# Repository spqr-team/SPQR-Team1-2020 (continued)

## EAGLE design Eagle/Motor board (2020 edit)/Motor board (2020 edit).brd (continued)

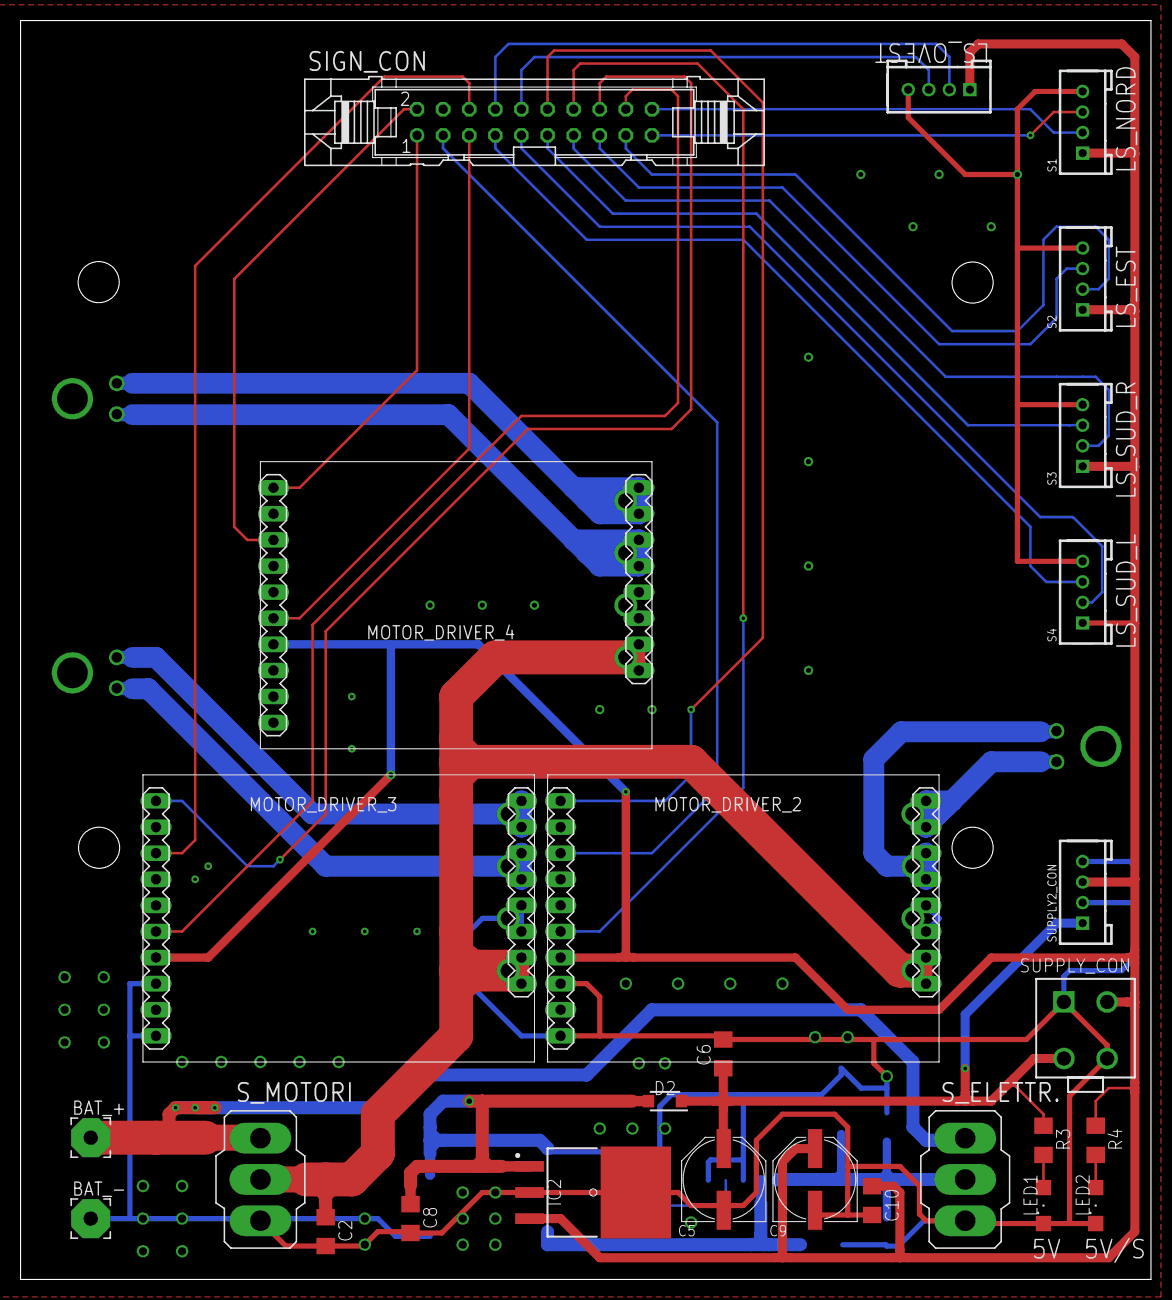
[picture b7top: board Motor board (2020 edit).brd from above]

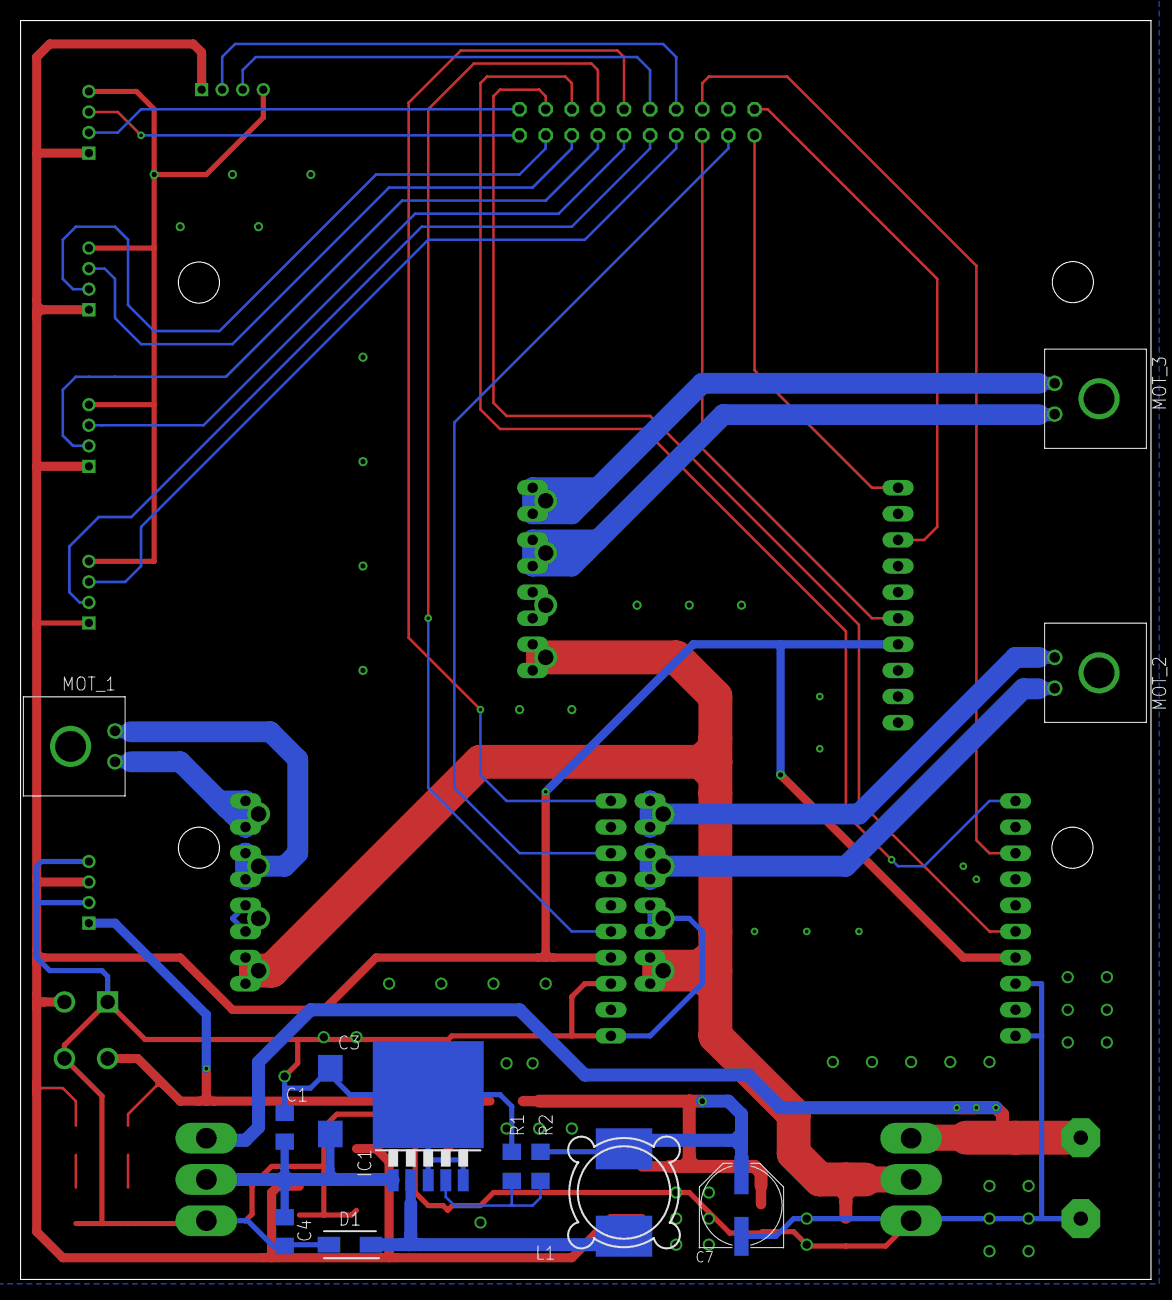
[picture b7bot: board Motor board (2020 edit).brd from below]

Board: 2 copper layers, 110.0 x 122.5 mm, 39 parts (12 on the bottom side), 36 nets.

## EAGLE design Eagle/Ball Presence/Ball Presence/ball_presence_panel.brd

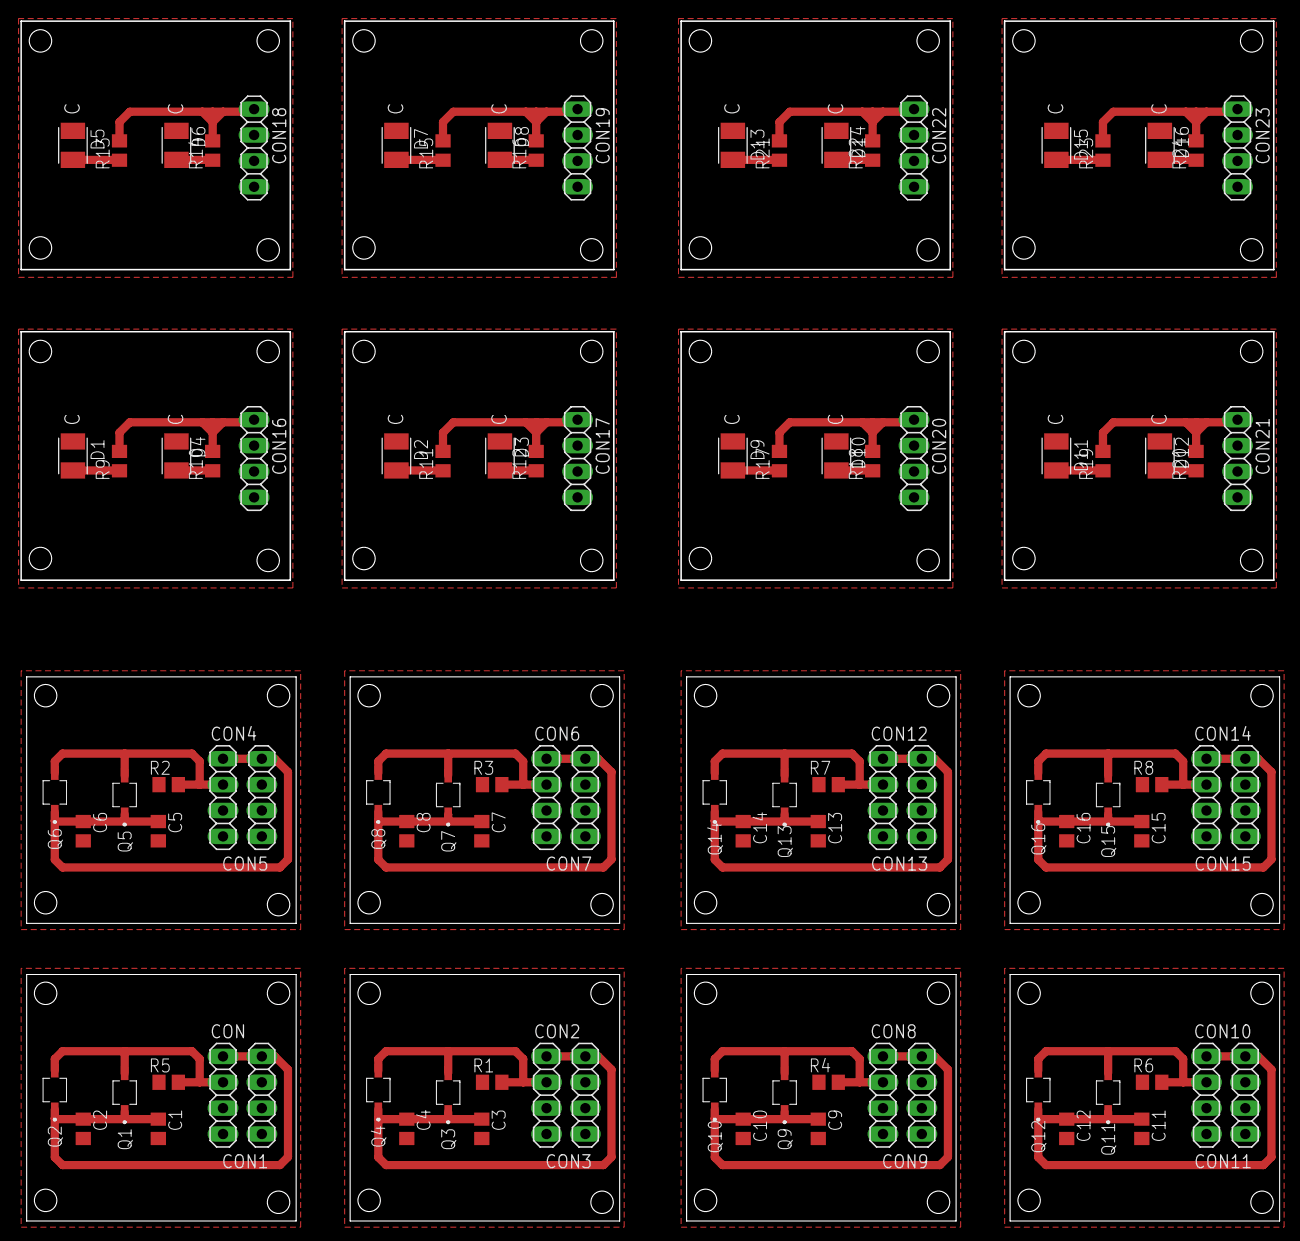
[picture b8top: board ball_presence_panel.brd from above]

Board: 2 copper layers, 123.5 x 117.8 mm, 96 parts (0 on the bottom side), 56 nets.

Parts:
C1, C2, C3, C4, C5, C6, C7, C8, C9, C10, C11, C12, C13, C14, C15, C16: C0805
CON, CON1, CON2, CON3, CON4, CON5, CON6, CON7, CON8, CON9, CON10, CON11, CON12, CON13, CON14, CON15, CON16, CON17, CON18, CON19, CON20, CON21, CON22, CON23: 1X04
D1, D2, D3, D4, D5, D6, D7, D8, D9, D10, D11, D12, D13, D14, D15, D16: 3528-2PIN
Q1, Q2, Q3, Q4, Q5, Q6, Q7, Q8, Q9, Q10, Q11, Q12, Q13, Q14, Q15, Q16: VEMT2520X01
R1, R2, R3, R4, R5, R6, R7, R8, R9, R10, R11, R12, R13, R14, R15, R16, R17, R18, R19, R20, R21, R22, R23, R24: R0805

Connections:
GND: C1.2, C2.2, CON.4, CON1.4, R5.1
GND1: C3.2, C4.2, CON2.4, CON3.4, R1.1
GND2: C5.2, C6.2, CON4.4, CON5.4, R2.1
GND3: C7.2, C8.2, CON6.4, CON7.4, R3.1
GND4: C9.2, C10.2, CON8.4, CON9.4, R4.1
GND5: C11.2, C12.2, CON10.4, CON11.4, R6.1
GND6: C13.2, C14.2, CON12.4, CON13.4, R7.1
GND7: C15.2, C16.2, CON14.4, CON15.4, R8.1
GND8: CON16.4, D1.1, D4.1
GND9: CON17.4, D2.1, D3.1
GND10: CON18.4, D5.1, D6.1
GND11: CON19.4, D7.1, D8.1
GND12: CON20.4, D9.1, D10.1
GND13: CON21.4, D11.1, D12.1
GND14: CON22.4, D13.1, D14.1
GND15: CON23.4, D15.1, D16.1
unnamed: D1.2, R9.1
unnamed: D2.2, R11.1
unnamed: D3.2, R12.1
unnamed: D4.2, R10.1
unnamed: D5.2, R13.1
unnamed: D6.2, R14.1
unnamed: D7.2, R15.1
unnamed: D8.2, R16.1
unnamed: D9.2, R17.1
unnamed: D10.2, R18.1
unnamed: D11.2, R19.1
unnamed: D12.2, R20.1
unnamed: D13.2, R21.1
unnamed: D14.2, R22.1
unnamed: D15.2, R23.1
unnamed: D16.2, R24.1
SIG1: CON.2, Q1.2, Q2.2, R5.2
SIG2: CON2.2, Q3.2, Q4.2, R1.2
SIG3: CON4.2, Q5.2, Q6.2, R2.2
SIG4: CON6.2, Q7.2, Q8.2, R3.2
SIG5: CON8.2, Q9.2, Q10.2, R4.2
SIG6: CON10.2, Q11.2, Q12.2, R6.2
SIG7: CON12.2, Q13.2, Q14.2, R7.2
SIG8: CON14.2, Q15.2, Q16.2, R8.2
V+: C1.1, C2.1, CON.1, CON1.1, Q1.1, Q2.1
V+1: C3.1, C4.1, CON2.1, CON3.1, Q3.1, Q4.1
V+2: C5.1, C6.1, CON4.1, CON5.1, Q5.1, Q6.1
V+3: C7.1, C8.1, CON6.1, CON7.1, Q7.1, Q8.1
V+4: C9.1, C10.1, CON8.1, CON9.1, Q9.1, Q10.1
V+5: C11.1, C12.1, CON10.1, CON11.1, Q11.1, Q12.1
V+6: C13.1, C14.1, CON12.1, CON13.1, Q13.1, Q14.1
V+7: C15.1, C16.1, CON14.1, CON15.1, Q15.1, Q16.1
V+8: CON16.1, R9.2, R10.2
V+9: CON17.1, R11.2, R12.2
V+10: CON18.1, R13.2, R14.2
V+11: CON19.1, R15.2, R16.2
V+12: CON20.1, R17.2, R18.2
V+13: CON21.1, R19.2, R20.2
V+14: CON22.1, R21.2, R22.2
V+15: CON23.1, R23.2, R24.2

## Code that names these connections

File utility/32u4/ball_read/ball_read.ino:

/**
  Sensor Mapping
    Sensor  Angle Pin Port
    S1      0     26  PD6
    S2            25  PD4
    S3            19  PD1
    S4            18  PD0
    S5      90    1   PE6
    S6            40  PF1
    S7            39  PF4
    S8            38  PF5
    S9      180   37  PF6
    S10           36  PF7
    S11           32  PC7
    S12           31  PC6
    S13     270   30  PB6
    S14           29  PB5
    S15           28  PB4
    S16           27  PD7
    loop cycle duration: 3.2 millis
**/

#define S5 ((PINE & 64 ) >> 6)

#define S11 ((PINC & 128 ) >> 7)
#define S12 ((PINC & 64 ) >> 6)

#define S13 ((PINB & 64 ) >> 6)
#define S14 ((PINB & 32 ) >> 5)
#define S15 ((PINB & 16) >> 4)

#define S1 ((PIND & 64 ) >> 6)
#define S2 ((PIND & 16 ) >> 4)
#define S3 ((PIND & 2 ) >> 1)
#define S4 (PIND & 1 )
#define S16 ((PIND & 128) >> 7)

#define S6 ((PINF & 2 ) >> 1)
#define S7 ((PINF & 16 ) >> 4)
#define S8 ((PINF & 32 ) >> 5)
#define S9 ((PINF & 64 ) >> 6)
#define S10 ((PINF & 128 ) >> 7)

#define NCYCLES 255
#define BROKEN  230
#define TOO_LOW 45

#define LED1ON (PORTD = PORTD | 0b00100000)
#define LED1OFF (PORTD = PORTD & 0b11011111)

#define LED2ON (PORTF = PORTF | 0b00000001)
#define LED2OFF (PORTF = PORTF & 0b11111110)

#define LED3ON (PORTB = PORTB | 0b10000000)
#define LED3OFF (PORTB = PORTB & 0b01111111)

#define LED4ON (PORTB = PORTB | 0b00000001)
#define LED4OFF (PORTB = PORTB & 0b11111110)


int counter[16];
int distance;
int nmax = 0;
int sensor = 0;

int oldIndex = 0;
int oldDistance = 0;

byte ballInfo = 0;

float xs[16];
float ys[16];

float angle = 0;
int dist = 0;
boolean sending = false;
byte sendAngle = 0, sendDistance = 0;
byte sendByte = 0;

unsigned long t = 0;

void setup() {
  delay(1000);

  Serial.begin(57600);
  Serial1.begin(57600);

  
  /*For now replace pinMode with writes to the direction register. 
    We don't know if pinMode will work on those sensors, and it has proven not be working on digitalWrite for reasons probably relative to compatibility between Arduino and our board,
    but this needs further investigation*/  

  //Set the LEDs as outputs, keep the rest as input by default

  //LED3(PB7) and LED4 (PB0)
  DDRB |= 0b10000001;
  //LED2 (PF0)
  DDRF |= 0b00000001;
  //LED1 (PD5)
  DDRD |= 0b00100000;
  
  /*pinMode(26, INPUT);   //S1
  pinMode(25, INPUT);   //S2
  pinMode(19, INPUT);   //S3
  pinMode(18, INPUT);   //S4
  pinMode(1, INPUT);    //S5
  pinMode(40, INPUT);   //S6
  pinMode(39, INPUT);   //S7
  pinMode(38, INPUT);   //S8
  pinMode(37, INPUT);   //S9
  pinMode(36, INPUT);   //S10
  pinMode(32, INPUT);   //S11
  pinMode(31, INPUT);   //S12
  pinMode(30, INPUT);   //S13
  pinMode(29, INPUT);   //S14
  pinMode(28, INPUT);   //S15
  pinMode(27, INPUT);   //S16*/
  
  for (int i = 0; i < 16; i++) {
    xs[i] = cos((22.5 * PI / 180) * i);
    ys[i] = sin((22.5 * PI / 180) * i);
  }
}

void loop() {
  readBallInterpolation();
  //printCounter();
  sendDataInterpolation();
  readFromTeensy();
  //test();
  //delay(100);
}

/**--- READ BALL USING SENSORS ANGLE INTERPOLATION ---**/

void readBallInterpolation() {
  for (int i = 0; i < 16; i++) {
    counter[i] = 0;
  }

  //reads from the register
  for (int i = 0; i < NCYCLES; i++) {
    counter[0] += !S1;
    counter[1] += !S2;
    counter[2] += !S3;
    counter[3] += !S4;
    counter[4] += !S5;
    counter[5] += !S6;
    counter[6] += !S7;
    counter[7] += !S8;
    counter[8] += !S9;
    counter[9] += !S10;
    counter[10] += !S11;
    counter[11] += !S12;
    counter[12] += !S13;
    counter[13] += !S14;
    counter[14] += !S15;
    counter[15] += !S16;
  }

  float x = 0, y = 0;
  for (int i = 0; i < 16; i++) {
    if (counter[i] > BROKEN || counter[i] < TOO_LOW) counter[i] = 0;

    x += xs[i] * counter[i];
    y += ys[i] * counter[i];
  }

  angle = atan2(y, x) * 180 / PI;
  angle = ((int)(angle + 360)) % 360;

  //distance is 0 when not seeing ball
  //dist = hypot(x, y);
  
  nmax = 0;
  //saves max value and sensor
  for (int i = 0; i < 16; i++) {
    if (counter[i] > nmax) {
      nmax = counter[i];
      sensor = i;
    }
  }

  distance = nmax;
  
  //turn led on
  if (distance == 0) {
    LED1OFF;
  } else {
    LED1ON;
  }
}

unsigned long sendtimer = 0;

void sendDataInterpolation() {
  //We must ensure that each number is expressed with three digits, adding leading zeros if necessary, to further improve transmission reliability
  String str_angle = String((int) angle, DEC);
  String str_distance = String(NCYCLES - (int) distance, DEC);

  String sendStr_angle = "";
  String sendStr_distance = "";

  if(str_angle.length() == 1) sendStr_angle = "00" + str_angle;
  else if(str_angle.length() == 2) sendStr_angle = "0" + str_angle;
  else sendStr_angle = str_angle;
  
  if(str_distance.length() == 1) sendStr_distance = "00" + str_distance;
  else if(str_distance.length() == 2) sendStr_distance = "0" + str_distance;
  else sendStr_distance = str_distance;

  //slow down the communciation a little bit, or it might get very messy
  if(millis() - sendtimer > 40){
    Serial1.print("b");
    Serial1.print(sendStr_angle);
    Serial1.print("-");
    Serial1.print(sendStr_distance);
    Serial1.print("IB");
    sendtimer = millis();
  }

}

void test() {
  readBallInterpolation();
  
  Serial1.println("===========");
  Serial1.print(S1);
  Serial1.print(" | ");
  Serial1.print(S2);
  Serial1.print(" | ");
  Serial1.print(S3);
  Serial1.print(" | ");
  Serial1.print(S4);
  Serial1.print(" | ");
  Serial1.print(S5);
  Serial1.print(" | ");
  Serial1.print(S6);
  Serial1.print(" | ");
  Serial1.print(S7);
  Serial1.print(" | ");
  Serial1.print(S8);
  Serial1.print(" | ");
  Serial1.print(S9);
  Serial1.print(" | ");
  Serial1.print(S10);
  Serial1.print(" | ");
  Serial1.print(S11);
  Serial1.print(" | ");
  Serial1.print(S12);
  Serial1.print(" | ");
  Serial1.print(S13);
  Serial1.print(" | ");
  Serial1.print(S14);
  Serial1.print(" | ");
  Serial1.print(S15);
  Serial1.print(" | ");
  Serial1.print(S16);
  Serial1.print(" ---  ");
  Serial1.println(sensor);
  Serial1.println("===========");
  delay(100);

}


void printCounter() {
  for (int i = 0; i < 16; i++) {
    Serial1.print(counter[i]);
    Serial1.print(" | ");
  }
    Serial1.print("\t\t| Angle: " );
    Serial1.print(angle);
    Serial1.print("||| Distance: " );
    Serial1.print(distance);
    
  Serial1.println();
  delay(100);
}

void readFromTeensy(){
  while(Serial1.available()){
    byte b = Serial1.read();
    if(b & 0b00000001 == 1) LED2ON;
    else LED2OFF;
    if((b & 0b00000010) >> 1 == 1) LED3ON;
    else LED3OFF;
    if((b & 0b00000100) >> 2 == 1) LED4ON;
    else LED4OFF;
  }
}

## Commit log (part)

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2019-10-09 culo
2019-10-14 culetto
2019-10-21 First class structure
2019-10-21 Maybe now it less confusing
2019-10-21 New code working with imu reading, tests are not working currently
2019-10-27 Branch classi latino, IMU MOT PID
2019-10-28 meno mot
2019-11-11 Added motor support, should work out of the box
2019-11-12 corretta una boiata
2019-11-13 Motors and recenter working
2019-11-14 init hardware
2019-11-18 adding a bit of polymorphism
2019-11-18 ball, maybe
2019-11-18 Using enums instead of ints for transmission protocols
2019-11-18 implemented camera
2019-11-18 added camera
2019-11-25 started working on the us sensors
2019-11-25 finished us, having trouble testing
2019-11-27 Error compiling, syntax should be better
2019-11-27 Finally us working
2019-12-02 US sensors using DataSourceController now working
2019-12-02 having troubles testing
2019-12-03 ema scemo
2019-12-04 first trial to follow the ball
2019-12-05 started writing goalie(), kinda dumb but seems to work
2019-12-05 Lines not working well, fixed missing initializations that caused the code to crash
2019-12-05 lines now working: angle of each motor was est to 0 in constructor
2019-12-05 sbubabub
2019-12-05 fixed something left by u-siri-ous
2019-12-09 ported goalie and keeper from old code, condtion code working to decide game strategy
2019-12-09 forgot to save a file
2019-12-11 started porting bt, corrected smth
2019-12-17 position
2019-12-20 started line_system to play properly
2019-12-26 reimproted the zone position system
2020-01-15 fixed a major issues with linesystems
2020-01-15 aaaa
2020-01-15 First camera script for conic shaped mirror
2020-01-20 conic shaped camera mirror final script
2020-01-20 new protocol for camera
2020-01-20 aaaaaaa
2020-01-22 first hardware commit
2020-01-22 working camera->teensy transimission protocol
2020-01-22 new goalie c:
2020-01-22 Teensy pinout done, supply almost done, IMU done
2020-01-22 Added motor drivers to schematic
2020-01-24 Added 32U4, created OpenMV4 library
2020-01-25 Added camera and IMU, ATmega32U4 pinout done, added motor drivers' leds
2020-01-26 Added motor connectors, added electrolytic cap on supply
2020-01-26 Calculating angles with the camera, have to be fixed with the 90 degrees offset. Uploading a little teesny <-> atmega32u4 test script for bidirectional relaiable serial communication
2020-01-27 Angles working?
2020-01-27 Angles finally working
2020-01-27 Added every component in BoM
2020-01-27 BoM finished
2020-01-28 Supply planes for motor drivers done
2020-01-29 reintroduces semi axis locking. Some bug with the lines make the robot stop when it gets on one. Tilt with vshaped mirror reintroduced
2020-01-31 Fixed camera angle reading from both openmv and teensy. Tilt from goalie kinda working now
2020-02-03 Camera angle correction using IMU should now work correctly
2020-02-03 Camera angle fix using IMU working once for all
2020-02-03 storcimento kinda working
2020-02-04 PCB layout almost done
2020-02-04 PCB almost done
2020-02-05 slight modifies to camera
2020-02-08 Fixed silkscreen errors
2020-02-10 Cleaned useless files, added datasheets
2020-02-10 Now using arduino PID library for movements. There probably a better way to use this, but it works for now
2020-02-10 corrected a few errors, Furio plays is more precise than ever when playing
2020-02-12 not working
2020-02-12 Added safety resistances on Teensy > VNH traces
2020-02-17 now latest complete structs are copied into new ones when updating status vector
2020-02-17 camera recenter (on x axis) working c:
2020-02-17 experimenting with y axis
2020-02-17 ema taking over
2020-02-17 slight edits to goalie
2020-02-17 Now using Flavio's PID Library, plays flawlessly
2020-02-18 Now using status vector everywhere :D (To be tested)
2020-02-21 New conic shaped mirror, works better. It's higher and has more noticeable changes on the y axis
2020-02-26 aaaaaaaaaaaaaaaaA
2020-02-26 camera pid testing
2020-02-26 complementary filter object
2020-02-27 now the robot can use the camera to recenter even when one the goals can't be seen
2020-02-28 Added RCWL compatible ToF
2020-02-28 camera working
2020-02-29 organized code in 5 folders, left vars.h and main.cpp out of them for easy changing purposes. also did two currently_unused folder in sensors for us and things soon-to-be taken out from the robot (li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
2020-02-29 updated README.md
    we now have names and such
2020-02-29 still README.md
    ocd much?
2020-03-02 little correction to the pid for position
2020-03-02 camera lines
2020-03-02 Corrected a few major bugs in camera data receiving and using. Still no lock trying to directly fix goals' coordinates using axis rotation formula.
2020-03-02 Job finished. Ready to print
2020-03-02 Create LICENSE
2020-03-03 added testMenu, to be tested
2020-03-03 still test menu, still to test
2020-03-09 edits in camera
2020-03-12 looking at past days' work
2020-03-12 fix last merge
2020-03-14 started thinking about goalie, to be tested, dunno if it works
2020-05-05 first commit, starting to work with a new setup
2020-05-05 removed data_source_us.h/.cpp, no US present on the 2021 robot, if needed, the files can be found in branch master
2020-05-06 fixed motor angles
2020-06-02 FILE DECRISTO
2020-10-29 implement test menu in main loop
2020-10-29 recycle striker strategy from last year code
    bad translation, goalie is actually a striker
2020-10-31 disable vector sum code for now
    calculations are a bitty crappy, think I found the bug for now (check added comments)
2020-10-31 a bit of recalibration for everything for the presentation game
2020-11-04 reorder files into system folders
    also rename Goalie to Striker because GRAMMAR
    (Goalie actually means keeper but we always intended it as a striker :D)
2020-11-21 port ball reading code to 32u4
2020-11-29 update ball_read to use registers instead of pinMode and digitalWrite also move all the files relative to 32u4 uC inside a dedicated folder add the Blink script i made to test if everything was worki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
2020-12-14 fix a "little" problematic derp in Main Board The labels for PowerBlock 4 's RC filter resistor and capacitor were inverted And so we soldered the components inverted, and we had a short between VCC 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
2020-12-17 test: add a couple of tests for 32u4
2021-01-11 pid: recalibrate pid
2021-01-11 use 5kHz as pwm frequency for motors So we don't get the motors stopping to turn when changing direction at high speeds because of current limit on the vnh7070
2021-01-11 systems: introduce empty systems for testing purposes
2021-01-11 do not update usCtrl They're not on the robot, they're not defined in the code, and updating them will just cause the whole thing to crash
2021-01-11 ball_read: tweak values for a good reading
2021-01-11 strategy: introduce a test striker with empty systems and set as only role
2021-01-11 movement: correct pid formula and motors angles
2021-01-15 bluetooth: sm2 test script
2021-01-31 game: fix order of updating that causes crashes
2021-01-31 camera: update scripts, line and position handling for H7
2021-01-31 roles: go back to normal striker
2021-01-31 pins: update buzzer and switches pins
2021-02-01 fix short between S11 and Multi1 GND
2021-02-01 do not initialize LEDs
    LEDs are hookep up to the AtMega32U4on the new board
    Some LED pins are hooked up to line sensors on the new board and caused them not to work properly
2021-02-22 new docs branch for docs, with a copy of the code just in case
2021-02-22 motors: ramp up and slow down of motors instead of bang.bang
2021-02-23 camera: tweaks to OpenMV script
    also add a control on the position of the blue goal
2021-03-01 remove old unused line systems
2021-03-01 striker: use striker based on old Latino's code
2021-03-01 sys-camera: a bit of recalibration
2021-03-01 motors: complementary filter on a per-motor speed
    avoid all the cons of bang-bang without spending 5mS ramping up and down
2021-03-01 add a missing pragma once
2021-03-01 positionsys camera: introduce an easy way to counter act bad mirror positioning This allows to define each point relative to the absolute center of the field shifting each Move Setpoint by a defined 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
2021-03-22 movement: enable vector sum for multiple movements in a single cycle
2021-03-29 ball sensor: ball angle in absolute space
2021-04-13 Final commit
2021-04-13 Switched powerblock 4 filter labels
2021-04-14 test menu: complete refactor
    and add camera tilt test
2021-04-14 complementary filter: default init of variable which may have caused crashes
2021-04-14 keeper: small value tweaking
2021-04-14 striker: robot tilt towards the goal when attacking Although without a roller the robot just sky-rockets the ball away when they come in touch
2021-04-14 position system camera & motors: proper vector sum, value tweaking
2021-04-14 OpenMV H7: avoid crash when blue goal isn't in sight
2021-04-19 Camera sensor: correct a massive freaking typo This caused a huge bug when testing the striker i'm dumb
2021-04-19 tilt: better tilt
2021-04-19 camera: coords filtering and better route calculation
2021-05-07 we now have a roller
2021-05-10 preparation for romecup: refine striker
2021-05-10 robocup preparation: fix lines add a workaround for when we don't see either of the goals add nice startup sounds
2021-05-10 drive: only drive when the PID is calculated no need to recalibrate the pid
2021-05-11 camera: translate camera points in raw data, not in position system
2021-05-12 robocup preparation: correct pos-sys-camera bugs better use of roller nice startup/debugging sounds disable auto gain in H7
2021-05-13 romecup: precision shooter
2021-05-13 mix fixes git decided to cancel
2021-05-13 precision shooter
2021-05-13 disable keeper for now
    as it looks like sometimes it blocks code execution
2021-05-13 --amend
2021-05-13 bluetooth, at last
2021-05-14 even better pass and shoot
2021-05-14 latest romecup code
2021-05-28 striker: follow the ball, pick it and score
    Our roller is about to fall apart and i have no specific sensor to detect the ball, which means in perfect conditions it works but it really doesn't in real world conditions
    Also we need to ameliorate the communication protocol between teensy and 32u4 in order to not lose precision
2021-05-29 ball: new ball reading algorithm, should improve precision
2021-06-07 initial ball presence sensors
    line sensors but small
2021-06-09 started dividing folders
2021-06-10 ball presence sensor v1.0
2021-06-20 ball presence sensor basically a line sensor with split led and phototransistors
2021-06-20 drive: fix to accept tilt values in the [0,360] range
2021-06-20 precision shooter: catch and spinning kick
2021-06-21 precision shooter,camera: improve, fix math error in translation alongside with better speed calculation and utility methods
2021-06-21 not used, using drive with new folders
2021-06-21 precision shooter: improve spinning kick
2021-06-22 precision shooter: catches ball and goes towards goal
    depending on the angle it catches the ball at, sometimes it hides the ball, sometimes it does a random spinning kick when it founds the line
2021-06-22 striker-roller: complete striker using the roller
2021-06-22 robocup: first technical challenge
    still could be better, faster and more precise in some parts
2021-06-23 a 'pecionata' of a technical challenge 1. 19 goals/min
    the robot needs to face the defensive goal and it just recenters. Maybe one day we will remake the spinning kick to account any situations
2021-06-23 superteam challenge: st challenge 1
2021-06-24 superteam challenges: challenge 3: spinner
2021-06-27 robocoup: tc2 - round robin
2021-06-27 ball: correctly detect when the ball is not present
2021-06-27 TC2: initial round robin
2021-06-27 pos-sys-camera: use IMU-fixed goal coordinates to calc position
2021-06-27 robocup: tc3: corner kick Co-authored-by: u-siri-ous <sanninosiria@gmail.com>
2021-06-27 end of rcj 2021 Co-authored-by: u-siri-ous <sanninosiria@gmail.com>
2021-12-05 pid: refine pid
